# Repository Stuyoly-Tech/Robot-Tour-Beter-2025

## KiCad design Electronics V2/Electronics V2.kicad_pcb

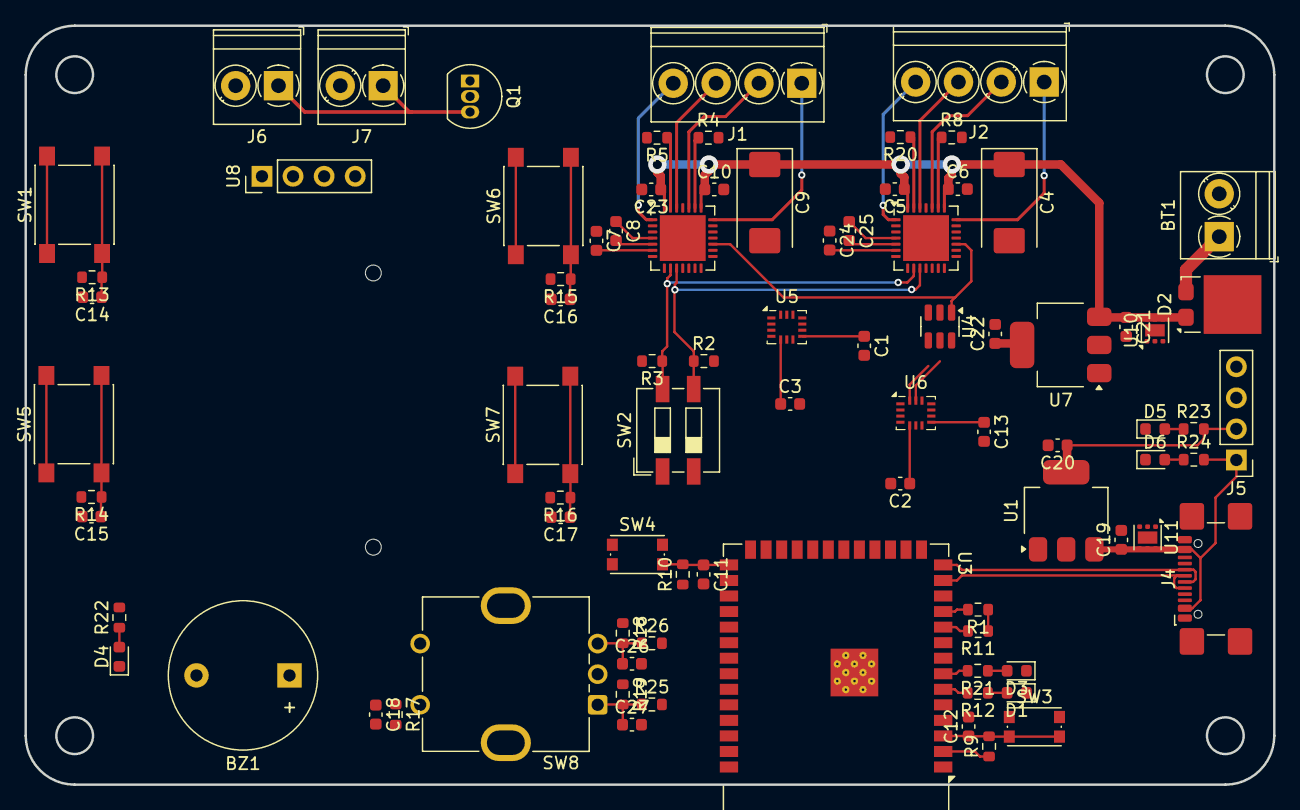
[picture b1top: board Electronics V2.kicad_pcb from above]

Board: 2 copper layers, 102.0 x 62.0 mm, 86 parts (1 on the bottom side), 65 nets.

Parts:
BT1: Battery; TerminalBlock_Phoenix_PT-1,5-2-3.5-H_1x02_P3.50mm_Horizontal
BZ1: Buzzer; Buzzer_12x9.5RM7.6
C1, C2, C3, C5, C6, C7, C10, C11, C12, C13, C14, C15, C16, C17, C18, C23, C24: 100n; C_0603_1608Metric
C4, C9: 100u; CP_EIA-7343-30_AVX-N
C8, C25: 22n; C_0603_1608Metric
C19, C20, C21, C22: 10u; C_0603_1608Metric
C26, C27: 10n; C_0603_1608Metric
D1: STATUS_LED; LED_0603_1608Metric
D2: D_Schottky; TO-277A
D3: LED_0; LED_0603_1608Metric
D4: LED_SD; LED_0603_1608Metric
D5: LED_3V3; LED_0603_1608Metric
D6: LED_5V; LED_0603_1608Metric
J1: MOT_L; TerminalBlock_Phoenix_PT-1,5-4-3.5-H_1x04_P3.50mm_Horizontal
J2: MOT_R; TerminalBlock_Phoenix_PT-1,5-4-3.5-H_1x04_P3.50mm_Horizontal
J3: SD_Card; SD_Hirose_DM1AA_SF_PEJ82
J4: USB_C_Receptacle_USB2.0_14P; USB_C_Receptacle_GCT_USB4110
J5: Power Probes; PinHeader_1x04_P2.54mm_Vertical
J6: L1; TerminalBlock_Phoenix_PT-1,5-2-3.5-H_1x02_P3.50mm_Horizontal
J7: L2; TerminalBlock_Phoenix_PT-1,5-2-3.5-H_1x02_P3.50mm_Horizontal
Q1: BC547; TO-92_Inline
R1, R2, R3, R9, R10, R11, R13, R14, R15, R16, R17, R18, R19, R25, R26: 10k; R_0603_1608Metric
R4, R5, R8, R20: 330m; R_0603_1608Metric
R12, R21, R22, R23: 1k; R_0603_1608Metric
R24: 1.5k; R_0603_1608Metric
SW1: BTN_0; SW_SPST_PTS645
SW2: MSTP_SEL; SW_DIP_SPSTx02_Slide_6.7x6.64mm_W6.73mm_P2.54mm_LowProfile_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
SW3: RST; SW_Push_1P1T_NO_CK_KMR2
SW4: BOOT; SW_Push_1P1T_NO_CK_KMR2
SW5: BTN_1; SW_SPST_PTS645
SW6: BTN_2; SW_SPST_PTS645
SW7: BTN_3; SW_SPST_PTS645
SW8: INCR_0; RotaryEncoder_Bourns_Vertical_PEC12R-3x17F-Sxxxx
U1, U7: NCP1117-3.3_SOT223; SOT-223-3_TabPin2
U2, U9: TMC2209; QFN-28-1EP_5x5mm_P0.5mm_EP3.75x3.75mm
U3: ESP32-S3-WROOM-1
U4: DAC081C081CIMK; SOT-23-6
U5: IMU_L; Bosch_LGA-14_3x2.5mm_P0.5mm
U6: IMU_R; Bosch_LGA-14_3x2.5mm_P0.5mm
U8: SSD1036; PinHeader_1x04_P2.54mm_Vertical
U10, U11: TVS1400DRV; WSON-6-1EP_2x2mm_P0.65mm_EP1x1.6mm

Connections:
+3V3: C1.1, C2.1, C3.1, C13.1, C20.1, C22.1, J3.4 (VDD), J5.2, R1.1, R9.1, R10.1, R11.1, R18.1, R19.1, R23.2, SW1.1, SW2.1, SW2.2, SW5.1, SW6.1, SW7.1, SW8.S2, U1.2 (VO), U2.15 (VCC_IO), U3.2 (3V3), U4.2 (VA), U5.5 (VDDI0), U5.8 (VDD), U5.12 (CSB), U6.1 (SDO), U6.5 (VDDI0), U6.8 (VDD), U6.12 (CSB), U7.2 (VO), U8.2 (VCC), U9.15 (VCC_IO)
+5V: C19.1, J4.A4 (VBUS), J4.A9 (VBUS), J4.B4 (VBUS), J4.B9 (VBUS), J5.1, Q1.1 (C), R24.2, U1.3 (VI), U2.8 (5VOUT), U9.8 (5VOUT), U11.4 (IN), U11.5 (IN), U11.6 (IN)
/BTN_0: C14.1, R13.1, SW1.2, U3.39 (IO1)
/BTN_1: C15.1, R14.1, SW5.2, U3.38 (IO2)
/BTN_2: C16.1, R15.1, SW6.2, U3.15 (IO3)
/BTN_3: C17.1, R16.1, SW7.2, U3.4 (IO4)
/BUZZER: BZ1.1 (+), U3.12 (IO8)
/CS_SD: J3.1 (CD/DAT3), U3.34 (IO41)
/D+: J4.A6 (D+), J4.B6 (D+), U3.14 (IO20)
/D-: J4.A7 (D-), J4.B7 (D-), U3.13 (IO19)
/DIAG_L: U2.11 (DIAG), U3.35 (IO42)
/DIAG_R: U3.25 (IO48), U9.11 (DIAG)
/DIR_L: U2.19 (DIR), U3.19 (IO11)
/DIR_R: U3.21 (IO13), U9.19 (DIR)
/INCR_A: R25.2, U3.8 (IO15)
/INCR_B: R26.2, U3.9 (IO16)
/INCR_BTN: C18.1, R17.1, SW8.S1, U3.5 (IO5)
/INDEX_L: U2.12 (INDEX), U3.24 (IO47)
/INDEX_R: U3.26 (IO45), U9.12 (INDEX)
/LASER: Q1.2 (B), U3.23 (IO21)
/MISO: J3.7 (DAT0), U3.32 (IO39)
/MOSI: J3.2 (CMD), U3.33 (IO40)
/Motor Driver_L/A1: J1.2, U2.24 (OA1)
/Motor Driver_L/A2: J1.1, U2.21 (OA2)
/Motor Driver_L/B1: J1.3, U2.26 (OB1)
/Motor Driver_L/B2: J1.4, U2.1 (OB2)
/Motor Driver_L/MS1_AD0: R3.1, SW2.4, U2.9 (MS1_AD0), U9.9 (MS1_AD0)
/Motor Driver_L/MS1_AD1: R2.1, SW2.3, U2.10 (MS1_AD1), U9.10 (MS1_AD1)
/Motor Driver_R/A1: J2.2, U9.24 (OA1)
/Motor Driver_R/A2: J2.1, U9.21 (OA2)
/Motor Driver_R/B1: J2.3, U9.26 (OB1)
/Motor Driver_R/B2: J2.4, U9.1 (OB2)
/SCL: R1.2, U3.11 (IO18), U4.5 (SCL), U5.13 (SCx), U6.13 (SCx), U8.3 (SCL)
/SCLK: J3.5 (CLK), U3.31 (IO38)
/SDA: R11.2, U3.10 (IO17), U4.4 (SDA), U5.14 (SDx), U6.14 (SDx), U8.4 (SDA)
/SPREAD: U2.7 (SPREAD), U3.22 (IO14), U9.7 (SPREAD)
/STEP_L: U2.16 (STEP), U3.18 (IO10)
/STEP_R: U3.20 (IO12), U9.16 (STEP)
/VREF: U2.17 (VREF), U4.1 (VOUT), U9.17 (VREF)
/~EN: U2.2 (ENN), U3.17 (IO9), U9.2 (ENN)
GND: BT1.2 (-), BZ1.2 (-), C1.2, C2.2, C3.2, C4.2, C5.2, C6.2, C9.2, C10.2, C11.2, C12.2, C13.2, C14.2, C15.2, C16.2, C17.2, C18.2, C19.2, C20.2, C21.2, C22.2, C23.2, C26.2, C27.2, D1.1 (K), D3.1 (K), D4.1 (K), D5.1 (K), D6.1 (K), J3.3 (VSS), J3.6 (VSS), J4.A1 (GND), J4.A12 (GND), J4.B1 (GND), J4.B12 (GND), J4.S1 (SHIELD), J5.3, J5.4, J6.2, J7.2, R2.2, R3.2, R4.2, R5.2, R8.2, R13.2, R14.2, R15.2, R16.2, R17.2, R20.2, SW3.1, SW4.1, SW8.C, U1.1 (GND), U2.3 (GND), U2.13 (CLK), U2.18 (GND), U2.29 (GND), U3.1 (GND), U3.16 (IO46), U3.40 (GND), U3.41 (GND), U4.3 (GND), U4.6 (ADR0), U5.1 (SDO), U5.6 (GNDI0), U5.7 (GND), U6.6 (GNDI0), U6.7 (GND), U7.1 (GND), U8.1 (GND), U9.3 (GND), U9.13 (CLK), U9.18 (GND), U9.29 (GND), U10.1 (GND), U10.2 (GND), U10.3 (GND), U10.7 (GND), U11.1 (GND), U11.2 (GND), U11.3 (GND), U11.7 (GND)
unnamed: BT1.1 (+), D2.2 (A)
unnamed: C26.1, R18.2, R26.1, SW8.B
unnamed: C27.1, R19.2, R25.1, SW8.A
unnamed: D1.2 (A), R12.1
unnamed: D3.2 (A), R21.1
unnamed: D4.2 (A), R22.1
unnamed: D5.2 (A), R23.1
unnamed: D6.2 (A), R24.1
unnamed: J6.1, J7.1, Q1.3 (E)
unnamed: R4.1, U2.23 (BRA)
unnamed: R5.1, U2.27 (BRB)
unnamed: C8.2, U2.5 (CPI)
unnamed: C8.1, U2.4 (CPO)
unnamed: C7.2, U2.6 (VCP)
unnamed: C12.1, R9.2, SW3.2, U3.3 (EN)
unnamed: C11.1, R10.2, SW4.2, U3.27 (IO0)
unnamed: R12.2, U3.6 (IO6)
unnamed: R21.2, U3.7 (IO7)
unnamed: R8.1, U9.23 (BRA)
unnamed: R20.1, U9.27 (BRB)
unnamed: C25.2, U9.5 (CPI)
unnamed: C25.1, U9.4 (CPO)
unnamed: C24.2, U9.6 (VCP)
VBAT: C4.1, C5.1, C6.1, C7.1, C9.1, C10.1, C21.1, C23.1, C24.1, D2.1 (K), U2.22 (VS), U2.28 (VS), U7.3 (VI), U9.22 (VS), U9.28 (VS), U10.4 (IN), U10.5 (IN), U10.6 (IN)

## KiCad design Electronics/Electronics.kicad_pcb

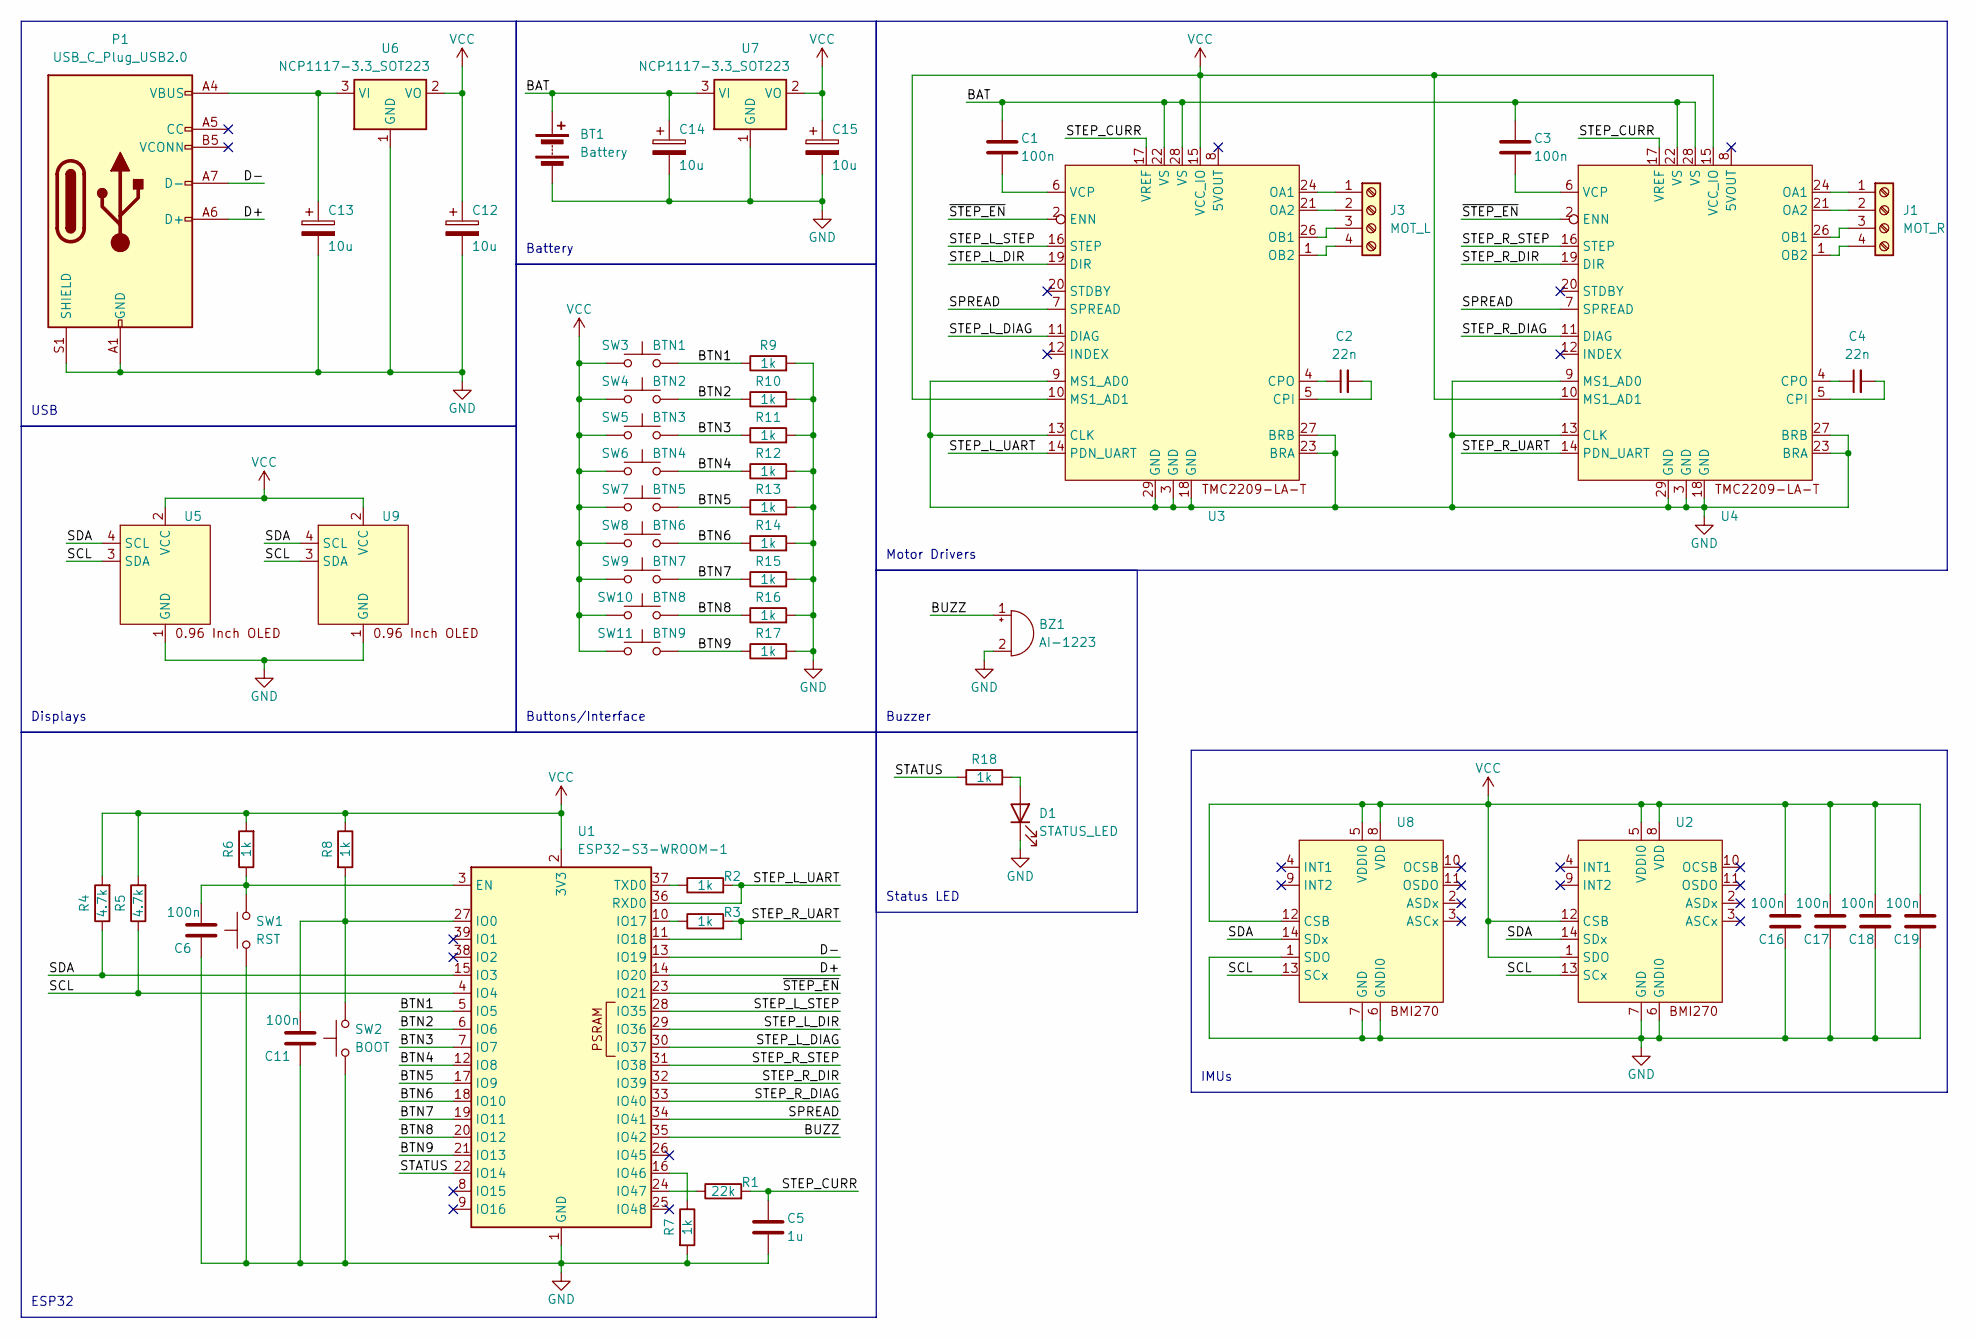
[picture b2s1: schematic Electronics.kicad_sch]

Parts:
BT1: Battery; TerminalBlock_Phoenix_PT-1,5-2-3.5-H_1x02_P3.50mm_Horizontal
BZ1: AI-1223; Buzzer_12x9.5RM7.6
C1, C3, C6, C11, C16, C17, C18, C19: 100n; C_0402_1005Metric
C2, C4: 22n; C_0402_1005Metric
C5: 1u; C_0603_1608Metric
C12, C13, C14, C15: 10u; C_0603_1608Metric
D1: STATUS_LED; LED_0603_1608Metric
J1: MOT_R; TerminalBlock_Phoenix_PT-1,5-4-3.5-H_1x04_P3.50mm_Horizontal
J3: MOT_L; TerminalBlock_Phoenix_PT-1,5-4-3.5-H_1x04_P3.50mm_Horizontal
P1: USB_C_Plug_USB2.0; USB_C_Receptacle_GCT_USB4110
R1: 22k; R_0201_0603Metric
R2, R3, R6, R7, R8, R9, R10, R11, R12, R13, R14, R15, R16, R17, R18: 1k; R_0201_0603Metric
R4, R5: 4.7k; R_0201_0603Metric
SW1: RST; SW_Push_1P1T_NO_CK_KMR2
SW2: BOOT; SW_Push_1P1T_NO_CK_KMR2
SW3: BTN1; SW_Push_1P1T_NO_CK_KMR2
SW4: BTN2; SW_Push_1P1T_NO_CK_KMR2
SW5: BTN3; SW_Push_1P1T_NO_CK_KMR2
SW6: BTN4; SW_Push_1P1T_NO_CK_KMR2
SW7: BTN5; SW_Push_1P1T_NO_CK_KMR2
SW8: BTN6; SW_Push_1P1T_NO_CK_KMR2
SW9: BTN7; SW_Push_1P1T_NO_CK_KMR2
SW10: BTN8; SW_Push_1P1T_NO_CK_KMR2
SW11: BTN9; SW_Push_1P1T_NO_CK_KMR2
U1: ESP32-S3-WROOM-1
U2, U8: Bosch_LGA-14_3x2.5mm_P0.5mm
U3, U4: QFN-28-1EP_5x5mm_P0.5mm_EP3.75x3.75mm
U5, U9: PinHeader_1x04_P2.54mm_Vertical
U6, U7: NCP1117-3.3_SOT223; SOT-223-3_TabPin2

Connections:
/BAT: BT1.1 (+), C1.1, C3.1, C14.1, U3.22 (VS), U3.28 (VS), U4.22 (VS), U4.28 (VS), U7.3 (VI)
/BTN1: R9.1, SW3.2, U1.5 (IO5)
/BTN2: R10.1, SW4.2, U1.6 (IO6)
/BTN3: R11.1, SW5.2, U1.7 (IO7)
/BTN4: R12.1, SW6.2, U1.12 (IO8)
/BTN5: R13.1, SW7.2, U1.17 (IO9)
/BTN6: R14.1, SW8.2, U1.18 (IO10)
/BTN7: R15.1, SW9.2, U1.19 (IO11)
/BTN8: R16.1, SW10.2, U1.20 (IO12)
/BTN9: R17.1, SW11.2, U1.21 (IO13)
/BUZZ: BZ1.1 (+), U1.35 (IO42)
/D+: P1.A6 (D+), U1.14 (IO20)
/D-: P1.A7 (D-), U1.13 (IO19)
/SCL: R5.1, U1.4 (IO4), U2.13 (SCx), U5.3 (SDA), U8.13 (SCx), U9.3 (SDA)
/SDA: R4.1, U1.15 (IO3), U2.14 (SDx), U5.4 (SCL), U8.14 (SDx), U9.4 (SCL)
/SPREAD: U1.34 (IO41), U3.7 (SPREAD), U4.7 (SPREAD)
/STATUS: R18.1, U1.22 (IO14)
/STEP_CURR: C5.1, R1.2, U3.17 (VREF), U4.17 (VREF)
/STEP_L_DIAG: U1.30 (IO37), U3.11 (DIAG)
/STEP_L_DIR: U1.29 (IO36), U3.19 (DIR)
/STEP_L_STEP: U1.28 (IO35), U3.16 (STEP)
/STEP_L_UART: R2.2, U1.36 (RXD0), U3.14 (PDN_UART)
/STEP_R_DIAG: U1.33 (IO40), U4.11 (DIAG)
/STEP_R_DIR: U1.32 (IO39), U4.19 (DIR)
/STEP_R_STEP: U1.31 (IO38), U4.16 (STEP)
/STEP_R_UART: R3.2, U1.11 (IO18), U4.14 (PDN_UART)
/~STEP_EN: U1.23 (IO21), U3.2 (ENN), U4.2 (ENN)
GND: BT1.2 (-), BZ1.2 (-), C5.2, C6.1, C11.1, C12.2, C13.2, C14.2, C15.2, C16.1, C17.1, C18.1, C19.1, D1.1 (K), P1.A1 (GND), P1.A12 (GND), P1.B1 (GND), P1.B12 (GND), P1.S1 (SHIELD), R7.2, R9.2, R10.2, R11.2, R12.2, R13.2, R14.2, R15.2, R16.2, R17.2, SW1.1, SW2.1, U1.1 (GND), U1.40 (GND), U1.41 (GND), U2.6 (GNDI0), U2.7 (GND), U3.3 (GND), U3.9 (MS1_AD0), U3.13 (CLK), U3.18 (GND), U3.23 (BRA), U3.27 (BRB), U3.29 (GND), U4.3 (GND), U4.9 (MS1_AD0), U4.13 (CLK), U4.18 (GND), U4.23 (BRA), U4.27 (BRB), U4.29 (GND), U5.1 (GND), U6.1 (GND), U7.1 (GND), U8.1 (SDO), U8.6 (GNDI0), U8.7 (GND), U9.1 (GND)
unnamed: D1.2 (A), R18.2
unnamed: J1.1, U4.24 (OA1)
unnamed: J1.2, U4.21 (OA2)
unnamed: J1.3, U4.26 (OB1)
unnamed: J1.4, U4.1 (OB2)
unnamed: J3.1, U3.24 (OA1)
unnamed: J3.2, U3.21 (OA2)
unnamed: J3.3, U3.26 (OB1)
unnamed: J3.4, U3.1 (OB2)
unnamed: C6.2, R6.1, SW1.2, U1.3 (EN)
unnamed: C11.2, R8.2, SW2.2, U1.27 (IO0)
unnamed: R3.1, U1.10 (IO17)
unnamed: R7.1, U1.16 (IO46)
unnamed: R1.1, U1.24 (IO47)
unnamed: R2.1, U1.37 (TXD0)
unnamed: C2.2, U3.5 (CPI)
unnamed: C2.1, U3.4 (CPO)
unnamed: C1.2, U3.6 (VCP)
unnamed: C4.2, U4.5 (CPI)
unnamed: C4.1, U4.4 (CPO)
unnamed: C3.2, U4.6 (VCP)
unnamed: C13.1, P1.A4 (VBUS), P1.A9 (VBUS), P1.B4 (VBUS), P1.B9 (VBUS), U6.3 (VI)
VCC: C12.1, C15.1, C16.2, C17.2, C18.2, C19.2, R4.2, R5.2, R6.2, R8.1, SW3.1, SW4.1, SW5.1, SW6.1, SW7.1, SW8.1, SW9.1, SW10.1, SW11.1, U1.2 (3V3), U2.1 (SDO), U2.5 (VDDI0), U2.8 (VDD), U2.12 (CSB), U3.10 (MS1_AD1), U3.15 (VCC_IO), U4.10 (MS1_AD1), U4.15 (VCC_IO), U5.2 (VCC), U6.2 (VO), U7.2 (VO), U8.5 (VDDI0), U8.8 (VDD), U8.12 (CSB), U9.2 (VCC)

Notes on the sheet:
Motor Drivers
Displays
Buttons/Interface
Buzzer
USB
IMUs
Status LED
ESP32
Battery

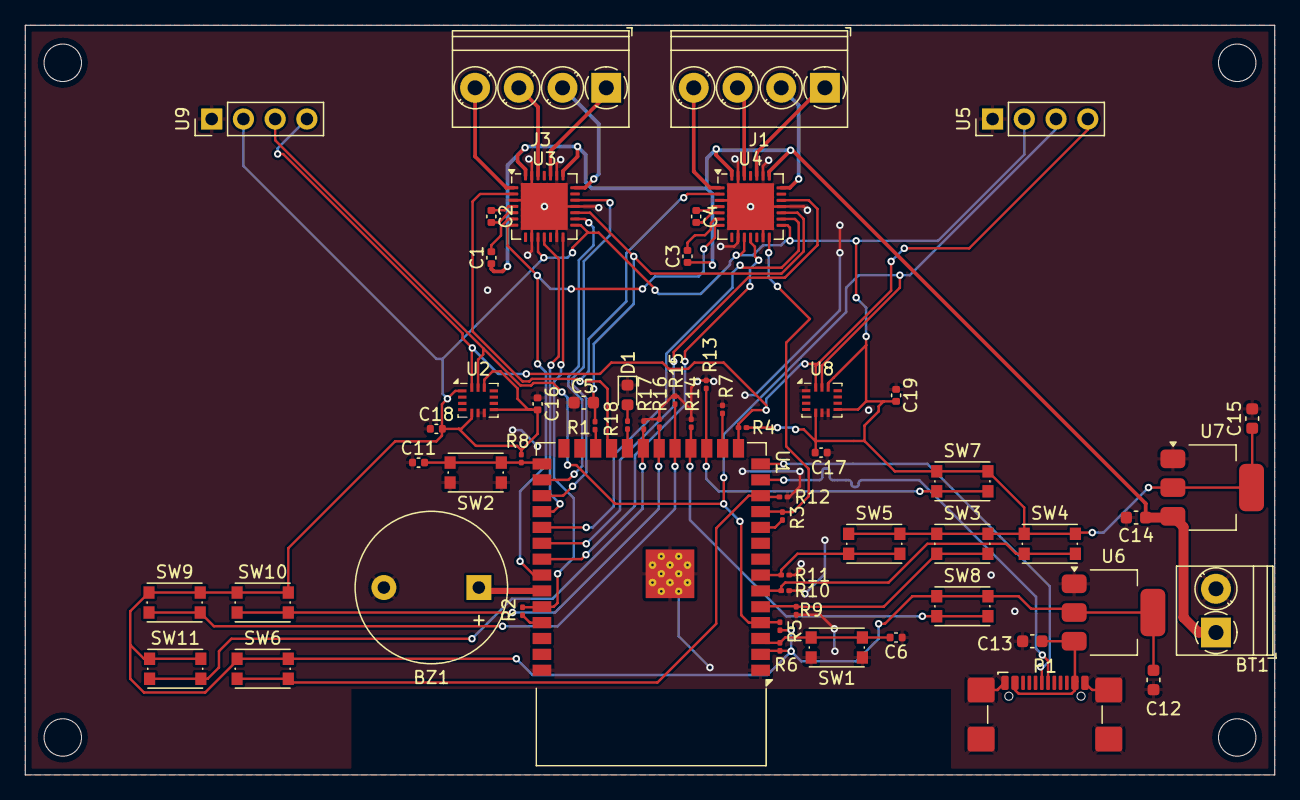
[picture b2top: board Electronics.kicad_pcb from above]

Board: 2 copper layers, 100.0 x 60.0 mm, 59 parts (0 on the bottom side), 51 nets.

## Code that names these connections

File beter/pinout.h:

#ifndef PINOUT_H
#define PINOUT_H

//Buttons for input(0 and 1 are swapped from pcb labeling)
#define BTN_0 2  //INIT | x
#define BTN_1 1  //RUN | TIME ADJUST
#define BTN_2 3  //ADJUSTMENTS | X ADJUST
#define BTN_3 4  //LASERS | Y ADJUST

//Rotary Encoder
#define INCR_BTN 5
#define INCR_A 15
#define INCR_B 16

//Indicatiors
#define BUZZER 8
#define LED_0 6
#define LED_1 7

//Motors
#define STEP_L 21
#define DIR_L 14
#define DIAG_L 48
#define INDEX_L 47

#define STEP_R 11
#define DIR_R 10
#define DIAG_R 13
#define INDEX_R 12

#define STEP_EN 9
#define SPREAD 45

//Laser
#define LASER 42

//SD Card
#define SD_CS 41
#define SD_CLK 38
#define SD_MOSI 40
#define SD_MISO 39

#endif

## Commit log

2025-01-28 work from amtrack
2025-01-28 oleds
2025-01-29 Schematics Done, footprints assigned
2025-01-30 started routing
2025-01-31 edging pcb done
2025-01-31 ready to manufacture, needs BOM, double checking
2025-02-03 production ready fr
2025-02-26 new board, needs usb, buttons, power, esd protection, transients, etc
2025-02-26 rotary encoder, buttons, needs esd, reverse voltage, usb, reg
2025-02-26 voltage regulators and oled
2025-02-26 needs footprints
2025-02-27 footprints
2025-02-27 ready ro route
2025-02-27 bc547 alternative
2025-02-27 routed power, etc
2025-03-01 placing done
2025-03-02 completed pcb (maybe)
2025-03-04 completed pcb fr this time
2025-03-04 added copper fill
2025-03-04 added copper fill + cleaning
2025-03-04 branch
2025-03-04 finish routing jit
2025-03-05 needs review
2025-03-06 copied the code hehehehaw
2025-03-12 starting to make menu functionality
2025-03-12 wrote driver loop except for Menu parts
2025-03-12 finished code for loop
2025-03-15 gyro code is there but its cooked
2025-03-15 it compiles now upload to bot tomorrow
2025-03-16 sd stuff no work
2025-03-16 sd card pins set
2025-03-17 DAC code
2025-03-18 fixed rotary encoder code
2025-03-18 dac works now
2025-03-18 no auto gyro init
2025-03-18 changed simplepursuit to floats
2025-03-19 pinout, etc
2025-03-19 controller combed through
2025-03-19 fell asleep
2025-03-19 Glued together codebase, needs testing
2025-03-19 i2c fix for DAC
2025-03-19 fixed compilation errors and compiled to robot
2025-03-19 need to test telemetry on linux
2025-03-19 need to fix gyro
2025-03-20 run constant speed and stall at the end
2025-03-20 added put default setvx call inside an else statement
2025-03-20 tuned? turning works!
2025-03-20 states?
2025-03-20 cool kinematics math calc
2025-03-20 doesn't slow at end'
2025-03-21 slows down at end (its geeked)
2025-03-21 hotel tuning !
2025-03-21 made it faster and now the stall should acc work fr fr
2025-03-21 pre states
2025-03-22 STATES CODE
2025-04-09 states version
2025-05-23 beter natsa
2025-05-24 NATS CODE
2025-10-20 states code restored (code for two bmi270s)
2025-10-21 Code fixed now path thingy imus
2025-10-21 we're using a bmi270 not bmi160 dpmo
2025-10-21 imu0 -> imu
2025-10-22 gate fixed
2025-10-22 fixed accidentally pasted code
2025-11-14 began to add bottle code
2025-11-14 compiles, need to implement logic in robot.cpp
2025-11-14 hopefully done with bottle logic
2025-11-15 fixed benjamins bottle logic
2025-12-19 code fixed ily checed
2025-12-19 runnable code
2025-12-20 pre bavf'
2025-12-20 JFSD
2025-12-20 error code
2025-12-23 tuning gyro drift
2026-01-06 its genuinely so good
2026-01-08 pre testing for mit
2026-01-09 fixed TT
2026-01-10 waiting for rubber
2026-01-13 hi benji
2026-02-10 post puso
2026-02-24 geeked ah codes couldnt run solon
2026-03-07 post soup
2026-03-13 jf;las lf;ds
2026-04-27 dac broken?
